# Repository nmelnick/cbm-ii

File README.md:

# cbm-ii

This repository contains code, utilities, and/or designs for the Commodore
CBM-II series of computers, more specifically the Commodore B128 that I work
with. Some contents here may support the many ways Commodore built and marketed
these, including the B256, B500, 610, 620, 630, 710, 620, 730, P500.

My online home for this machine is
https://www.nmelnick.com/the-vintage-collection/commodore-b128/

## Contents

* [psu-meanwell-bracket](psu-meanwell-bracket): Bracket to mount a Meanwell
  RT-65B power supply in the B128 case
* [teensy-keyboard](teensy-keyboard): Source code for interfacing the keyboard
  to a modern USB computer using a Teensy++ 2.0
* [tick-circuit](tick-circuit): Create a 50/60 Hz square wave tick circuit from
  a 5V input

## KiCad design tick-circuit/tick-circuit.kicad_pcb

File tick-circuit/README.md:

# tick-circuit

This is a work in progress, largely copied from the
[Mix and Tick](http://aminet.net/package/docs/hard/Mix_and_Tick)
by Michael Schulz.

This will take a +5V and GND input from a power supply and output a 50 or 60 Hz
square wave from J2, depending on the quartz crystal placed at X1. This circuit
has been prototyped with the 3.93216 MHz crystal, providing 60 Hz. The V1
and V2 circuits have been ordered and used successfully in a Commodore B128. 

## BOM

| Part                 | Quantity | Location |
| -------------------- | -------- | -------- |
| 74HCT4060            | 1        | U1       |
| 74HCT73              | 1        | U2       |
| 10M Resistor         | 1        | R1       |
| 100K Resistor        | 1        | R2       |
| 6.8pF Capacitor      | 2        | C1, C2   |
| 100nF Capacitor      | 2        | C3, C4   |
| Bournier 2p Block    | 1        | J1       |
| Metz 360272 1p Block | 1        | J2       |
| 3.93216 MHz Xtal     | 1        | X1       |

3.93216 MHz Xtal can be replaced with a 3.2768 MHz for 50 Hz output.

The terminal block pads can be directly soldered to if you're feeling wild.

## Resources

This uses the logic-4000 libraries from https://github.com/alexisvl/kicad-schlib

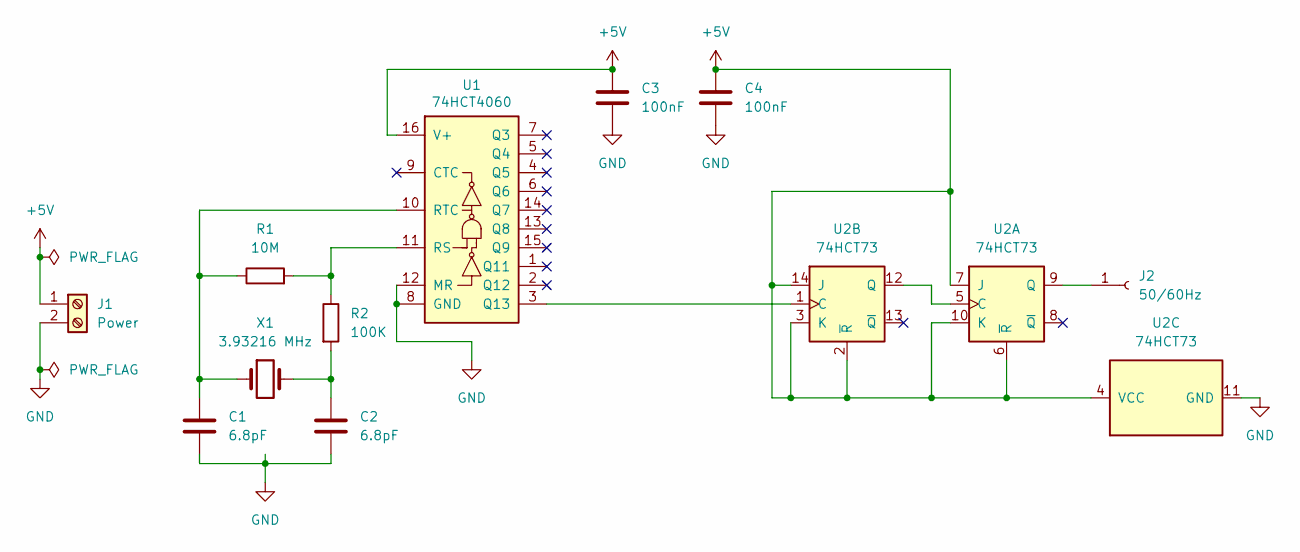
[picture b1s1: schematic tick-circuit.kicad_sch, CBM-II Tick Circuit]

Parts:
C1, C2: 6.8pF; C_Disc_D4.7mm_W2.5mm_P5.00mm
C3, C4: 100nF; C_Disc_D4.7mm_W2.5mm_P5.00mm
J1: Power; TerminalBlock_bornier-2_P5.08mm
J2: 50/60Hz; TerminalBlock_MetzConnect_360272_1x01_Horizontal_ScrewM2.6
R1: 10M; R_Axial_DIN0207_L6.3mm_D2.5mm_P10.16mm_Horizontal
R2: 100K; R_Axial_DIN0207_L6.3mm_D2.5mm_P10.16mm_Horizontal
U1: 74HCT4060; DIP-16_W7.62mm_Socket
U2: 74HCT73; DIP-14_W7.62mm_Socket
X1: 3.93216 MHz; Crystal_HC49-4H_Vertical

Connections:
+5V: C3.1, C4.1, J1.1, U1.16 (V+), U2.2 (~R), U2.3 (K), U2.4 (VCC), U2.6 (~R), U2.7 (J), U2.10 (K), U2.14 (J)
GND: C1.2, C2.2, C3.2, C4.2, J1.2, U1.8 (GND), U1.12 (MR), U2.11 (GND)
unnamed: C2.1, R2.2, X1.2
unnamed 3: J2.1, U2.9 (Q); also elsewhere on the board
unnamed: U1.3 (Q13), U2.1 (C)
unnamed: R1.2, R2.1, U1.11 (RS)
unnamed: C1.1, R1.1, U1.10 (RTC), X1.1
unnamed: U2.5 (C), U2.12 (Q)

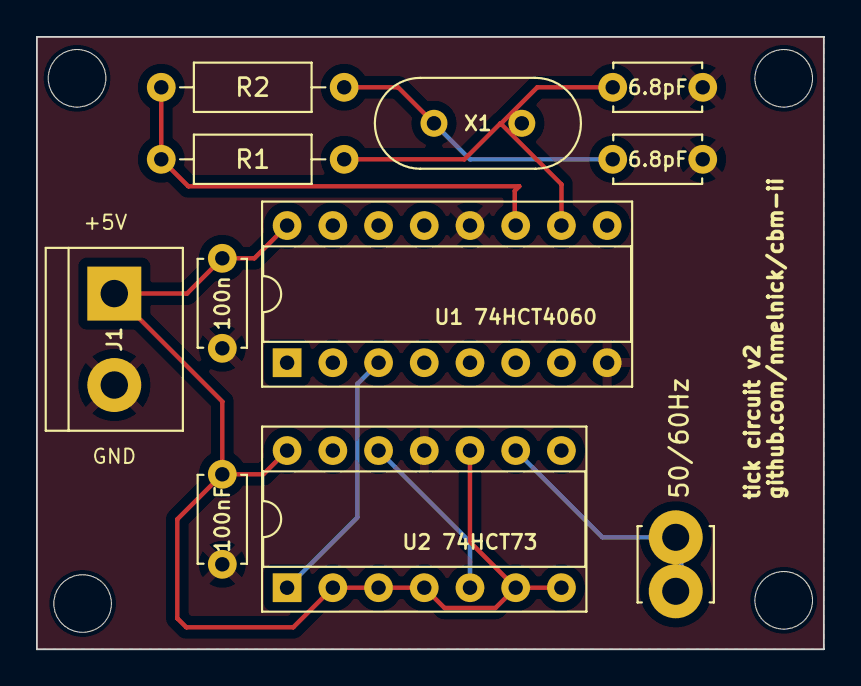
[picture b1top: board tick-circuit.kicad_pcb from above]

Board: 2 copper layers, 43.7 x 34.0 mm, 11 parts (0 on the bottom side), 8 nets.

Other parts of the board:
50/60Hz: 50/60Hz; TerminalBlock_MetzConnect_360272_1x01_Horizontal_ScrewM2.6

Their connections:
unnamed 3: 50/60Hz.1; also elsewhere on the board

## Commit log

2023-11-12 Initial commit, with teensy-keyboard
2023-11-12 Update README and add current round of the bracket
2023-11-16 README bump
2023-11-16 Add PSU Meanwell bracket (#1)
    * Update README and add current round of the bracket
    * README bump
2023-11-16 wip tick circuit
2023-11-16 Move meanwell bracket further over to the side to add room on the other, add ventilation slats
2023-11-17 First round of PCB, but no idea what I am doing
2023-11-17 Use both layers, add ground fills
2023-11-17 No need for ground routing if it is all ground
2023-11-17 Board was uneven
2023-11-18 Misconnected +5v to the connection from U1 to U2, which would have sucked
2023-11-18 I like to move it move it
2023-11-18 Add mounting holes for the current iteration of the tick circuit
2023-11-18 Create a tick circuit, with all of the knowledge that I have no idea what I am doing (#2)
    * wip tick circuit
    * First round of PCB, but no idea what I am doing
    * Use both layers, add ground fills
    * No need for ground routing if it is all ground
    * Board was uneven
    * Update README
2023-11-18 Add tick-circuit to README
2023-11-18 Increase ventilation slat size, move tick circuit down 1mm
2023-11-23 Change resistor footprints, change J2 footprint, alter routing to match, move 5v away from gnd, add URL to pcb
2023-11-23 Add gerber
2023-11-23 Tick circuit fixes (#4)
    * Change resistor footprints, change J2 footprint, alter routing to match, move 5v away from gnd, add URL to pcb
    * Add gerber
2023-11-23 Update PSU bracket to add ventilation and mount the tick circuit (#3)
    * Move meanwell bracket further over to the side to add room on the other, add ventilation slats
    * Add mounting holes for the current iteration of the tick circuit
    * Increase ventilation slat size, move tick circuit down 1mm
2023-11-23 Extend mounting holes by 1mm to be flush with ribs
2023-11-23 Add name of project
2023-11-23 Change gerber to zip
2023-11-23 Shrink 3mm from psu bracket, add one more ventilation slat between rib and bracket
2025-03-08 Adjust bracket to allow the side to face the keyboard, leaving more room on the back of the case
2025-04-24 Tick Circuit v2, an altered layout of the board to fit the electrical paths better
2025-06-18 Update gerber
2025-07-01 Update resistor footprint to hold a larger one, update README to show test success
